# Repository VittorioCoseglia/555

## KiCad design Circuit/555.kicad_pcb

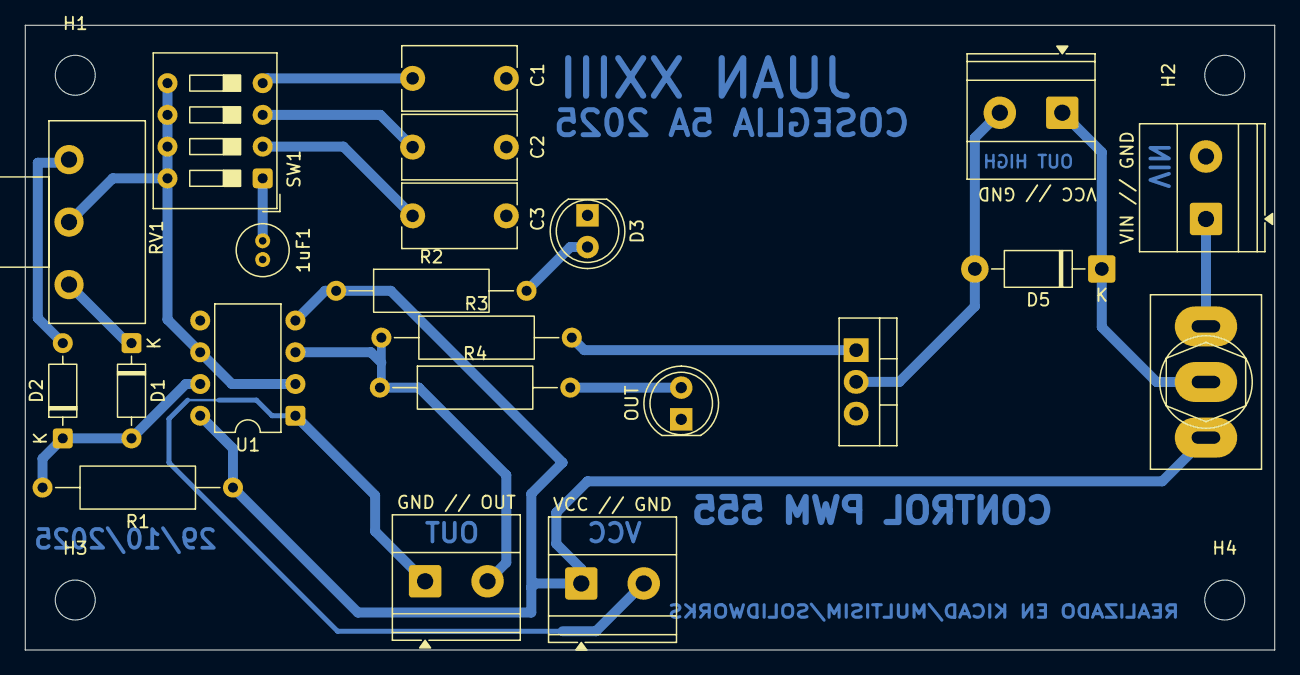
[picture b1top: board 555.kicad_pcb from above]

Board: 2 copper layers, 100.0 x 50.0 mm, 26 parts (0 on the bottom side), 17 nets.

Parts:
1uF1: C4; C_Radial_D4.0mm_H7.0mm_P1.50mm
C1: 1nF; C_Disc_D9.0mm_W5.0mm_P7.50mm
C2: 10nF; C_Disc_D9.0mm_W5.0mm_P7.50mm
C3: 100n; C_Disc_D9.0mm_W5.0mm_P7.50mm
D1, D2: 1N4148; D_DO-35_SOD27_P7.62mm_Horizontal
D3: LED; LED_D5.0mm
D5: 1N4007; D_DO-41_SOD81_P10.16mm_Horizontal
GND // OUT: OUT; TerminalBlock_Phoenix_MKDS-1,5-2_1x02_P5.00mm_Horizontal
H1, H2, H3, H4: MountingHole; MountingHole_3.2mm_M3
OUT: LED; LED_D5.0mm
Q1: TIP122; TO-220-3_Vertical
R1, R3: 1K; R_Axial_DIN0309_L9.0mm_D3.2mm_P15.24mm_Horizontal
R2, R4: 220; R_Axial_DIN0309_L9.0mm_D3.2mm_P15.24mm_Horizontal
RV1: 50K; Potentiometer_Piher_T-16H_Single_Horizontal
SW1: SW_DIP_x04; SW_DIP_SPSTx04_Slide_9.78x12.34mm_W7.62mm_P2.54mm
SW2: SW_SPDT; SW_Toggle_Blue_wSlots
U1: NE555P; DIP-8_W7.62mm
VCC // GND: OUT DARLINGTONG; TerminalBlock_Phoenix_MKDS-1,5-2_1x02_P5.00mm_Horizontal
VCC // GND#2: VCC--GND; TerminalBlock_Phoenix_MKDS-1,5-2_1x02_P5.00mm_Horizontal
VIN // GND: VIN; TerminalBlock_Phoenix_MKDS-1,5-2_1x02_P5.00mm_Horizontal

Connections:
+5V: R1.1, R2.1, SW2.1 (A), U1.4 (R), U1.8 (VCC), VCC // GND#2.1
GND: 1uF1.2, C1.2, C2.2, C3.2, D3.1 (K), GND // OUT.1, OUT.1 (K), Q1.3 (E), U1.1 (GND), VCC // GND#2.2, VIN // GND.2
unnamed: 1uF1.1, SW1.1
unnamed: C1.1, SW1.4
unnamed: C2.1, SW1.3
unnamed: C3.1, SW1.2
unnamed: D1.2 (A), D2.1 (K), R1.2, U1.7 (DIS)
unnamed: D1.1 (K), RV1.3
unnamed: D2.2 (A), RV1.1
unnamed: D3.2 (A), R2.2
unnamed: OUT.2 (A), R4.2
unnamed: D5.2 (A), Q1.2 (C), VCC // GND.2
unnamed: D5.1 (K), SW2.2 (B), VCC // GND.1
unnamed: GND // OUT.2, R3.1, R4.1, U1.3 (Q)
unnamed: SW2.3 (C), VIN // GND.1
unnamed: Q1.1 (B), R3.2
unnamed: RV1.2, SW1.5, SW1.6, SW1.7, SW1.8, U1.2 (TR), U1.6 (THR)
